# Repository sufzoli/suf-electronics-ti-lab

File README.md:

# suf-electronics-ti-lab
Replica of TI precision lab evaluation board

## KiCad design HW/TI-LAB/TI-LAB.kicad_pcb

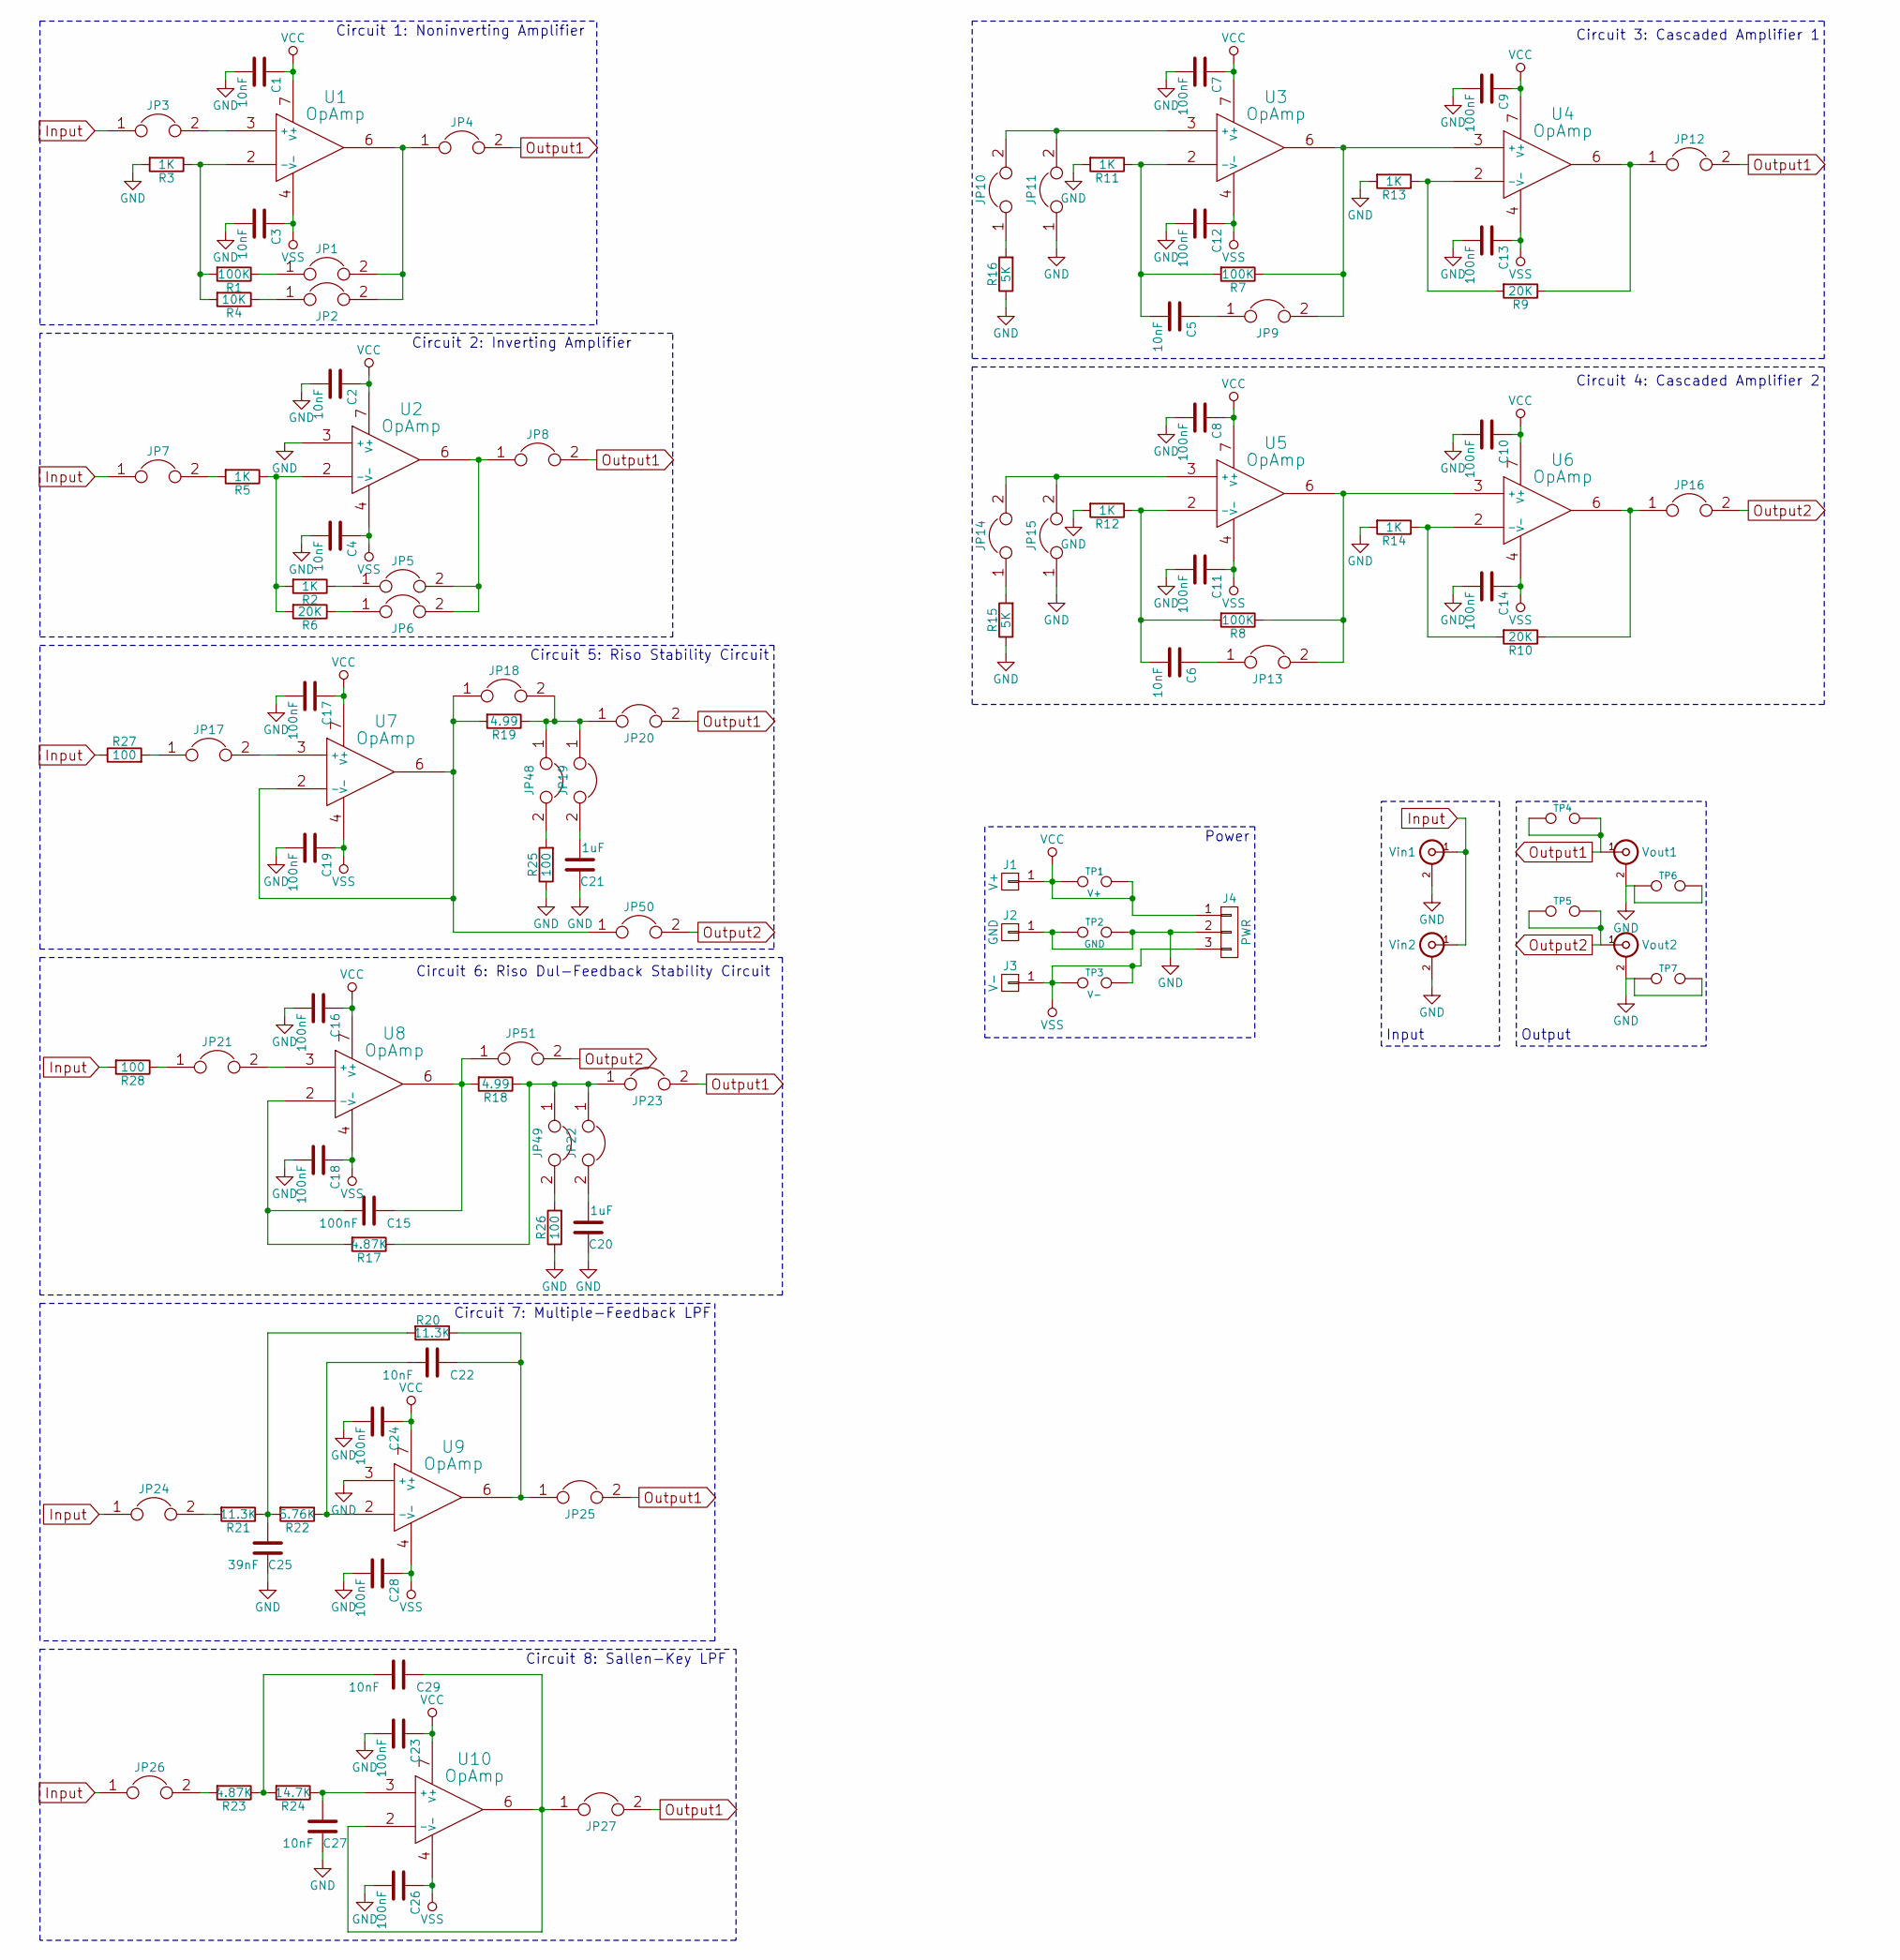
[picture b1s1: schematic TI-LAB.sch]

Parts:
C1, C2, C3, C4, C5, C6, C22, C27, C29: 10nF; C_0805_HandSoldering
C7, C8, C9, C10, C11, C12, C13, C14, C15, C16, C17, C18, C19, C23, C24, C26, C28: 100nF; C_0805_HandSoldering
C20, C21: 1uF; C_0805_HandSoldering
C25: 39nF; C_0805_HandSoldering
J1: V+; BANANA
J2: GND; BANANA
J3: V-; BANANA
J4: PWR; CONN_NCW254-03S
JP1, JP2, JP3, JP4, JP5, JP6, JP7, JP8, JP9, JP10, JP11, JP12, JP13, JP14, JP15, JP16, JP17, JP18, JP19, JP20, JP21, JP22, JP23, JP24, JP25, JP26, JP27, JP48, JP49, JP50, JP51: Pin_Header_Straight_1x02
R1, R7, R8: 100K; R_0805_HandSoldering
R2, R3, R5, R11, R12, R13, R14: 1K; R_0805_HandSoldering
R4: 10K; R_0805_HandSoldering
R6, R9, R10: 20K; R_0805_HandSoldering
R15, R16: 5K; R_0805_HandSoldering
R17, R23: 4.87K; R_0805_HandSoldering
R18, R19: 4.99; R_0805_HandSoldering
R20, R21: 11.3K; R_0805_HandSoldering
R22: 5.76K; R_0805_HandSoldering
R24: 14.7K; R_0805_HandSoldering
R25, R26, R27, R28: 100; R_0805_HandSoldering
TP1: V+; Pin_Header_Straight_1x02
TP2: GND; Pin_Header_Straight_1x02
TP3: V-; Pin_Header_Straight_1x02
TP4, TP5, TP6, TP7: Pin_Header_Straight_1x02
U1, U2, U3, U4, U5, U6, U7, U8, U9, U10: OpAmp; DIP-8_W7.62mm_LongPads
Vin1, Vin2: BNC_Socket_TYCO-AMP_LargePads
Vout1, Vout2: BNC_Socket_TYCO-AMP_LargePads

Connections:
GND: C1.2, C2.2, C3.2, C4.2, C7.2, C8.2, C9.2, C10.2, C11.2, C12.2, C13.2, C14.2, C16.2, C17.2, C18.2, C19.2, C20.1, C21.1, C23.2, C24.2, C25.1, C26.2, C27.1, C28.2, J2.1, J4.2, JP11.1, JP15.1, R3.2, R11.2, R12.2, R13.2, R14.2, R15.1, R16.1, R25.1, R26.1, TP2.1, TP2.2, TP6.1, TP6.2, TP7.1, TP7.2, U2.3 (+), U9.3 (+), Vin1.2 (Ext), Vin2.2 (Ext), Vout1.2 (Ext), Vout2.2 (Ext)
Input: JP3.1, JP7.1, JP24.1, JP26.1, R27.1, R28.2, Vin1.1 (In), Vin2.1 (In)
unnamed: C5.1, JP9.1
unnamed: C5.2, R7.2, R11.1, U3.2 (-)
unnamed: C6.1, JP13.1
unnamed: C6.2, R8.2, R12.1, U5.2 (-)
unnamed: C15.1, JP51.1, R18.2, U8.6
unnamed: C15.2, R17.2, U8.2 (-)
unnamed: C20.2, JP22.2
unnamed: C21.2, JP19.2
unnamed: C22.1, JP25.1, R20.1, U9.6
unnamed: C22.2, R22.1, U9.2 (-)
unnamed: C25.2, R20.2, R21.1, R22.2
unnamed: C27.2, R24.1, U10.3 (+)
unnamed: C29.1, JP27.1, U10.2 (-), U10.6
unnamed: C29.2, R23.1, R24.2
unnamed: JP1.1, R1.1
unnamed: JP1.2, JP2.2, JP4.1, U1.6
unnamed: JP2.1, R4.1
unnamed: JP3.2, U1.3 (+)
unnamed: JP5.1, R2.1
unnamed: JP5.2, JP6.2, JP8.1, U2.6
unnamed: JP6.1, R6.1
unnamed: JP7.2, R5.2
unnamed: JP9.2, R7.1, U3.6, U4.3 (+)
unnamed: JP10.1, R16.2
unnamed: JP10.2, JP11.2, U3.3 (+)
unnamed: JP12.1, R9.1, U4.6
unnamed: JP13.2, R8.1, U5.6, U6.3 (+)
unnamed: JP14.1, R15.2
unnamed: JP14.2, JP15.2, U5.3 (+)
unnamed: JP16.1, R10.1, U6.6
unnamed: JP17.1, R27.2
unnamed: JP17.2, U7.3 (+)
unnamed: JP18.1, JP50.1, R19.2, U7.2 (-), U7.6
unnamed: JP18.2, JP19.1, JP20.1, JP48.1, R19.1
unnamed: JP21.1, R28.1
unnamed: JP21.2, U8.3 (+)
unnamed: JP22.1, JP23.1, JP49.1, R17.1, R18.1
unnamed: JP24.2, R21.2
unnamed: JP26.2, R23.2
unnamed: JP48.2, R25.2
unnamed: JP49.2, R26.2
unnamed: R1.2, R3.1, R4.2, U1.2 (-)
unnamed: R2.2, R5.1, R6.2, U2.2 (-)
unnamed: R10.2, R14.1, U6.2 (-)
unnamed: R9.2, R13.1, U4.2 (-)
Output1: JP4.2, JP8.2, JP12.2, JP20.2, JP23.2, JP25.2, JP27.2, TP4.1, TP4.2, Vout1.1 (In)
Output2: JP16.2, JP50.2, JP51.2, TP5.1, TP5.2, Vout2.1 (In)
VCC: C1.1, C2.1, C7.1, C8.1, C9.1, C10.1, C16.1, C17.1, C23.1, C24.1, J1.1, J4.1, TP1.1, TP1.2, U1.7 (V+), U2.7 (V+), U3.7 (V+), U4.7 (V+), U5.7 (V+), U6.7 (V+), U7.7 (V+), U8.7 (V+), U9.7 (V+), U10.7 (V+)
VSS: C3.1, C4.1, C11.1, C12.1, C13.1, C14.1, C18.1, C19.1, C26.1, C28.1, J3.1, J4.3, TP3.1, TP3.2, U1.4 (V-), U2.4 (V-), U3.4 (V-), U4.4 (V-), U5.4 (V-), U6.4 (V-), U7.4 (V-), U8.4 (V-), U9.4 (V-), U10.4 (V-)

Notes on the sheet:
Circuit 1: Noninverting Amplifier
Input
Circuit 2: Inverting Amplifier
Output
Circuit 3: Cascaded Amplifier 1
Circuit 4: Cascaded Amplifier 2
Circuit 5: Riso Stability Circuit
Circuit 6: Riso Dul-Feedback Stability Circuit
Circuit 7: Multiple-Feedback LPF
Circuit 8: Sallen-Key LPF
Power

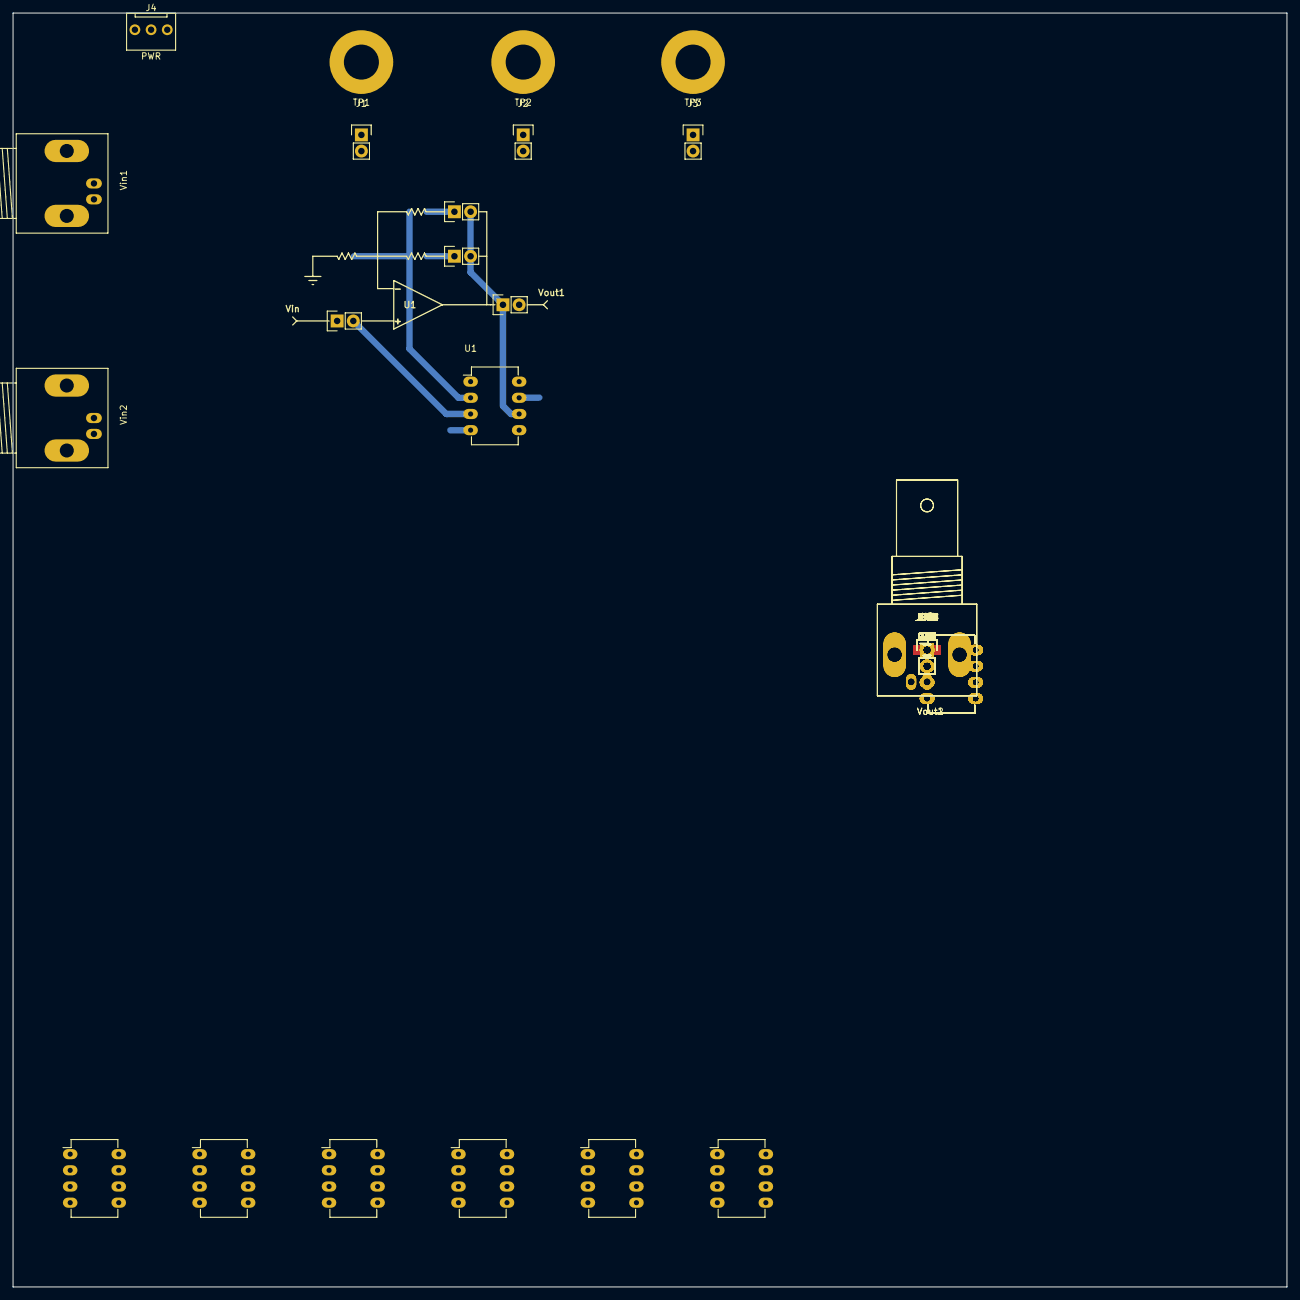
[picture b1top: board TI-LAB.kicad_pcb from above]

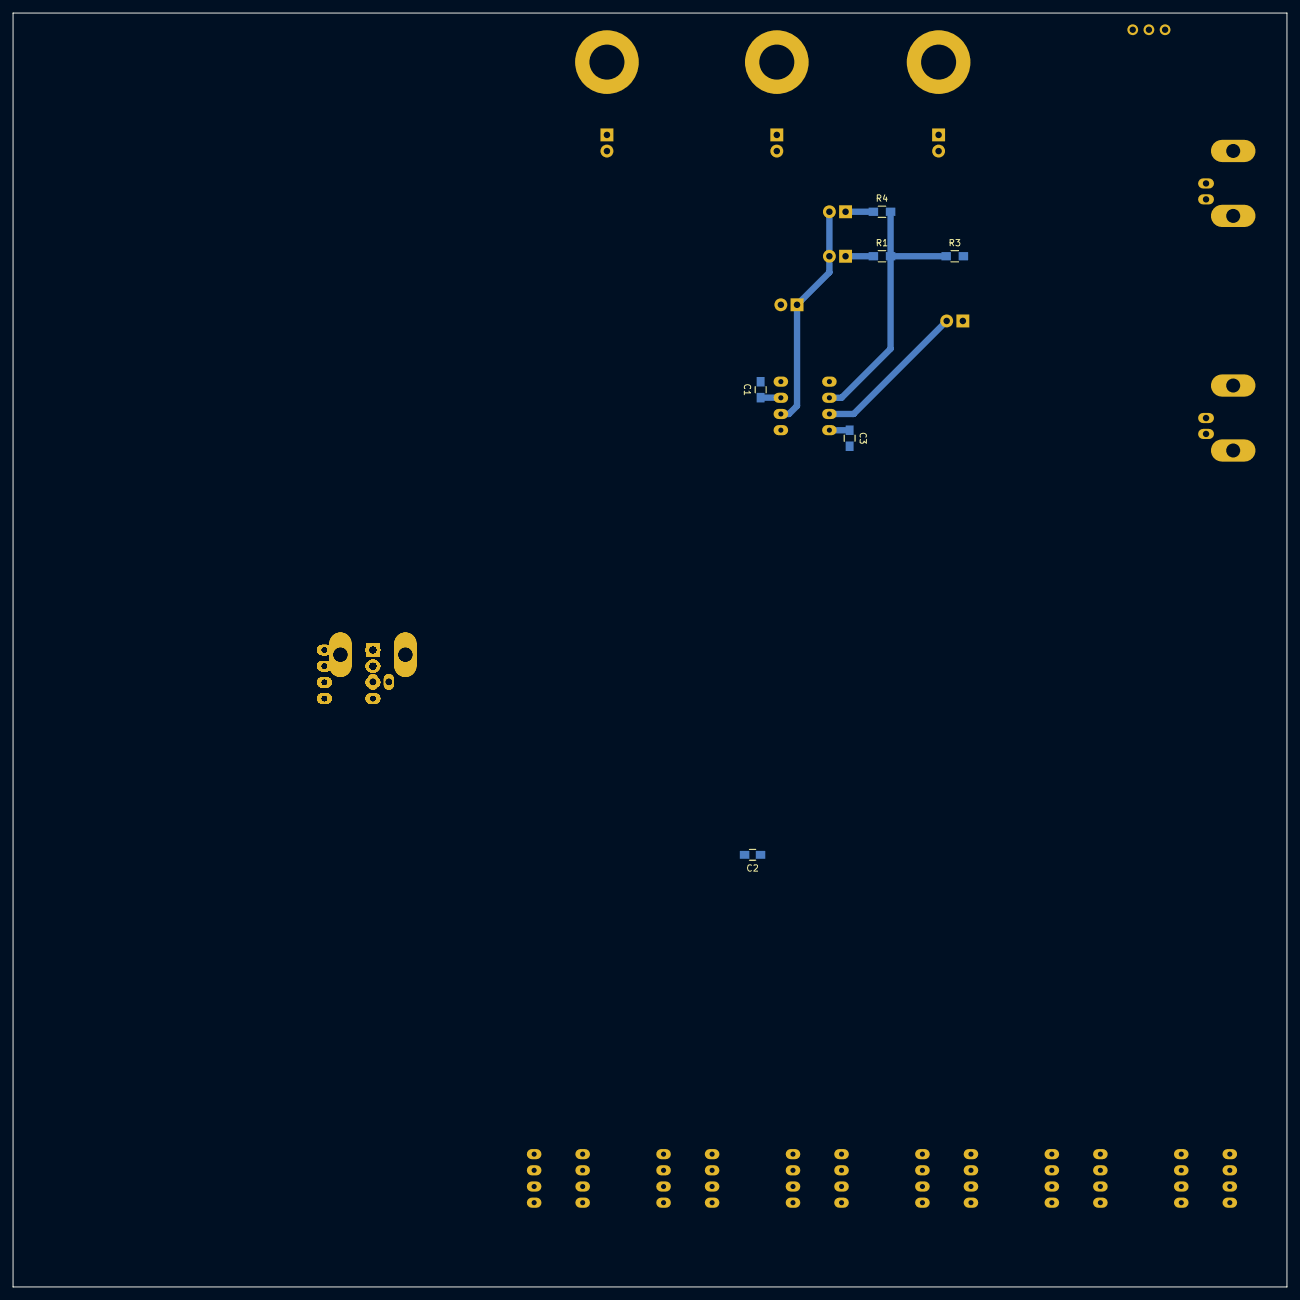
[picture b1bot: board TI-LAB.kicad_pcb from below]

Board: 2 copper layers, 200.0 x 200.0 mm, 113 parts (6 on the bottom side), 51 nets.

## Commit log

2015-06-07 Schematic Added
2021-03-20 add reimaing - archive
